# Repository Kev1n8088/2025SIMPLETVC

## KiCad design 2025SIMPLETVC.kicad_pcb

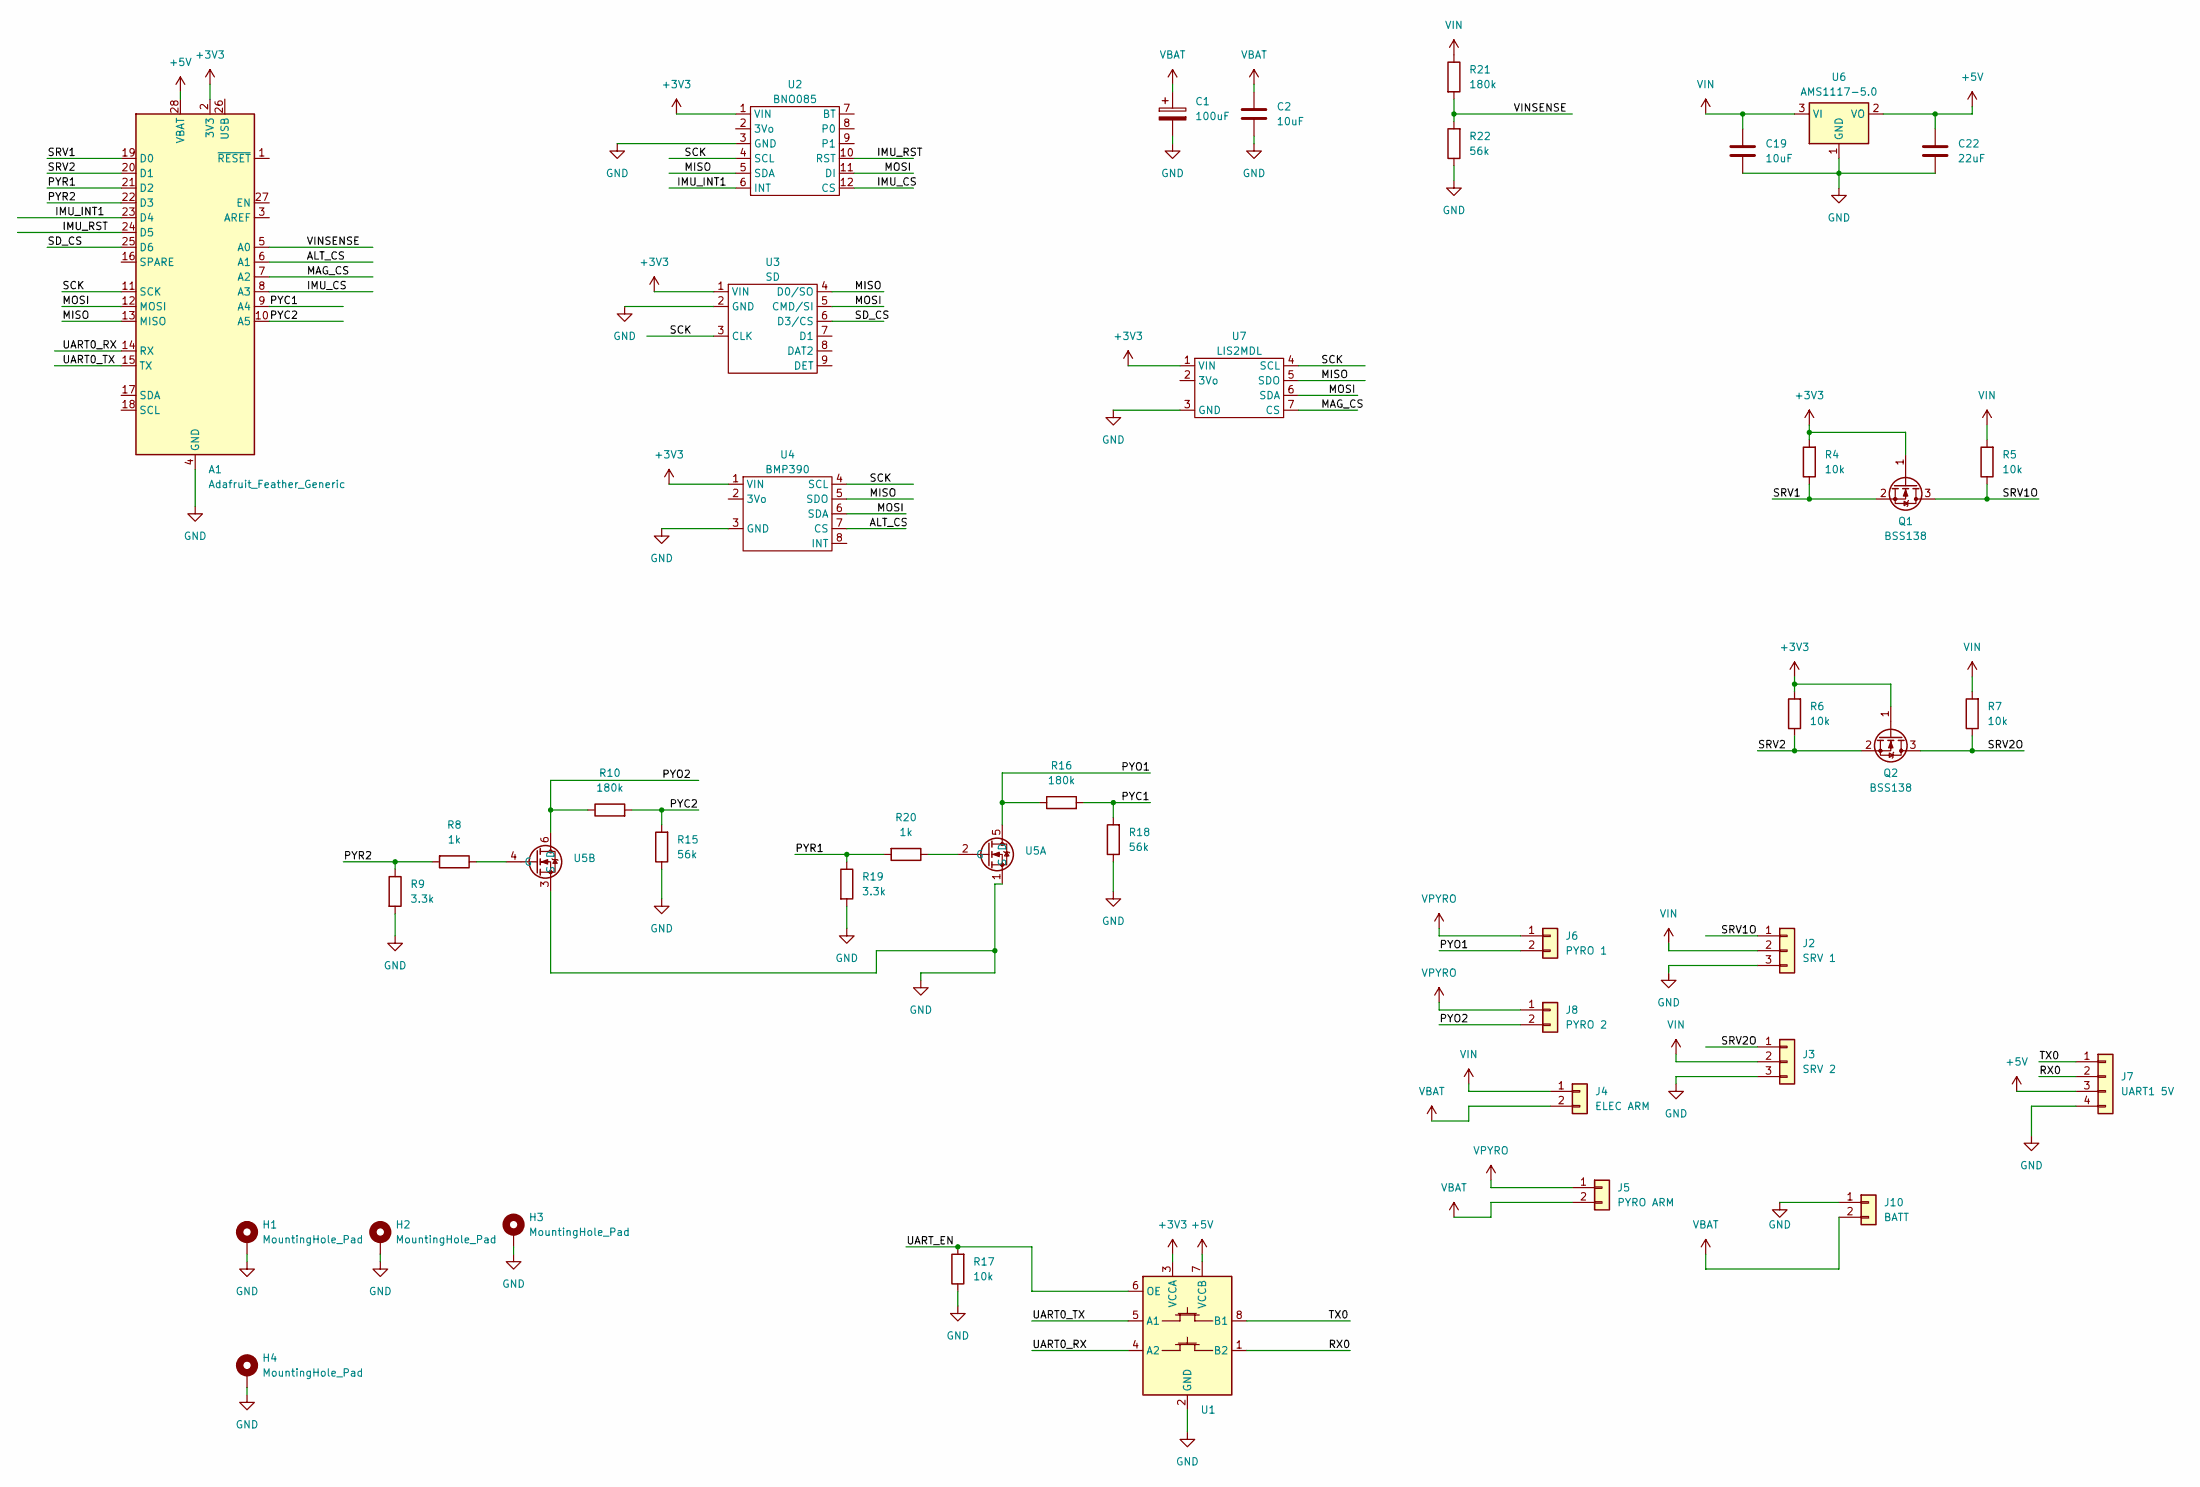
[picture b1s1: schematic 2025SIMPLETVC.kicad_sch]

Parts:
A1: Adafruit_Feather_Generic; Adafruit_Feather
C1: 100uF; CP_Radial_D8.0mm_P5.00mm
C2, C19: 10uF; C_0402_1005Metric
C22: 22uF; C_0402_1005Metric
H1, H2, H3, H4: MountingHole_Pad; MountingHole_4.3mm_M4_DIN965_Pad_TopBottom
J2: SRV 1; JST_XH_B3B-XH-AM_1x03_P2.50mm_Vertical
J3: SRV 2; JST_XH_B3B-XH-AM_1x03_P2.50mm_Vertical
J4: ELEC ARM; JST_XH_B2B-XH-AM_1x02_P2.50mm_Vertical
J5: PYRO ARM; JST_XH_B2B-XH-AM_1x02_P2.50mm_Vertical
J6: PYRO 1; JST_XH_B2B-XH-AM_1x02_P2.50mm_Vertical
J7: UART1 5V; JST_PH_B4B-PH-K_1x04_P2.00mm_Vertical
J8: PYRO 2; JST_XH_B2B-XH-AM_1x02_P2.50mm_Vertical
J10: BATT; AMASS_XT30U-F_1x02_P5.0mm_Vertical
Q1, Q2: BSS138; SOT-23
R4, R5, R6, R7, R17: 10k; R_0402_1005Metric
R8, R20: 1k; R_0402_1005Metric
R9, R19: 3.3k; R_0402_1005Metric
R10, R16, R21: 180k; R_0402_1005Metric
R15, R18, R22: 56k; R_0402_1005Metric
U1: TXS0102DCT; SSOP-8_2.95x2.8mm_P0.65mm
U2: BNO085; BNO085_Breakout_Footprint
U3: SD; SD_Breakout_Footprint
U4: BMP390; BMP390_Breakout_Footprint
U5: SQJ500AEP-T1_GE3_VIS
U6: AMS1117-5.0; SOT-223-3_TabPin2
U7: LIS2MDL; LIS2MDL_Breakout_Footprint

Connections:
+3V3: A1.2 (3V3), Q1.1 (G), Q2.1 (G), R4.2, R6.2, U1.3 (VCCA), U2.1 (VIN), U3.1 (VIN), U4.1 (VIN), U7.1 (VIN)
+5V: A1.28 (VBAT), C22.1, J7.3, U1.7 (VCCB), U6.2 (VO)
/ALT_CS: A1.6 (A1), U4.7 (CS)
/IMU_CS: A1.8 (A3), U2.12 (CS)
/IMU_INT1: A1.23 (D4), U2.6 (INT)
/IMU_RST: A1.24 (D5), U2.10 (RST)
/MAG_CS: A1.7 (A2), U7.7 (CS)
/MISO: A1.13 (MISO), U2.5 (SDA), U3.4 (D0/SO), U4.5 (SDO), U7.5 (SDO)
/MOSI: A1.12 (MOSI), U2.11 (DI), U3.5 (CMD/SI), U4.6 (SDA), U7.6 (SDA)
/PYC1: A1.9 (A4), R16.2, R18.2
/PYC2: A1.10 (A5), R10.2, R15.2
/PYO1: J6.2, R16.1, U5.5 (D)
/PYO2: J8.2, R10.1, U5.6 (D)
/PYR1: A1.21 (D2), R19.1, R20.2
/PYR2: A1.22 (D3), R8.2, R9.1
/RX0: J7.2, U1.1 (B2)
/SCK: A1.11 (SCK), U2.4 (SCL), U3.3 (CLK), U4.4 (SCL), U7.4 (SCL)
/SD_CS: A1.25 (D6), U3.6 (D3/CS)
/SRV1: A1.19 (D0), Q1.2 (S), R4.1
/SRV1O: J2.1, Q1.3 (D), R5.1
/SRV2: A1.20 (D1), Q2.2 (S), R6.1
/SRV2O: J3.1, Q2.3 (D), R7.1
/TX0: J7.1, U1.8 (B1)
/UART0_RX: A1.14 (RX), U1.4 (A2)
/UART0_TX: A1.15 (TX), U1.5 (A1)
/UART_EN: R17.2, U1.6 (OE)
/VINSENSE: A1.5 (A0), R21.2, R22.2
GND: A1.4 (GND), C1.2, C2.2, C19.2, C22.2, H1.1, H2.1, H3.1, H4.1, J2.3, J3.3, J7.4, J10.1, R9.2, R15.1, R17.1, R18.1, R19.2, R22.1, U1.2 (GND), U2.3 (GND), U3.2 (GND), U4.3 (GND), U5.1 (S), U5.3 (S), U6.1 (GND), U7.3 (GND)
unnamed: R20.1, U5.2 (G)
unnamed: R8.1, U5.4 (G)
VBAT: C1.1, C2.1, J4.2, J5.2, J10.2
VIN: C19.1, J2.2, J3.2, J4.1, R5.2, R7.2, R21.1, U6.3 (VI)
VPYRO: J5.1, J6.1, J8.1

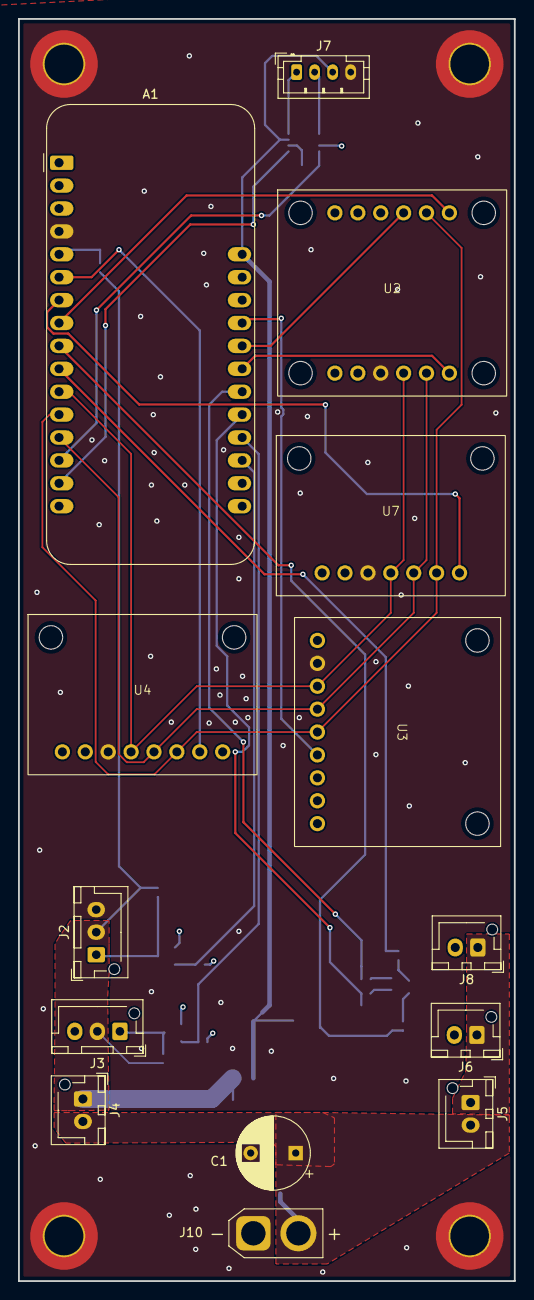
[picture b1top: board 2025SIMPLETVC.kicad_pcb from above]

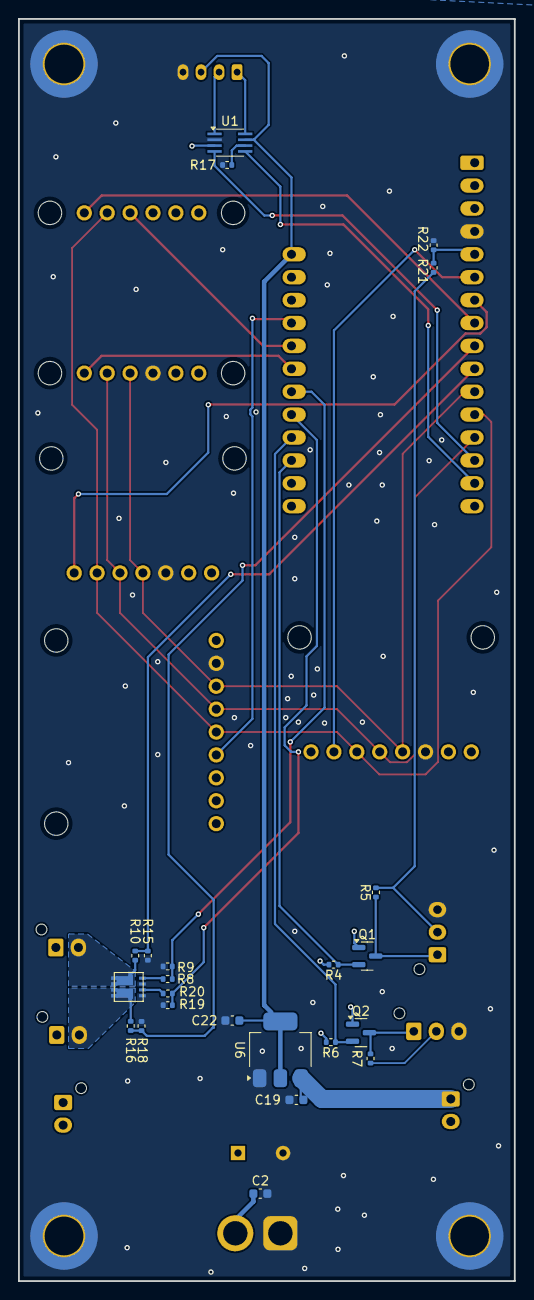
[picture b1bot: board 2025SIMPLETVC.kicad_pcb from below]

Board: 4 copper layers, 55.0 x 140.0 mm, 41 parts (23 on the bottom side), 33 nets.

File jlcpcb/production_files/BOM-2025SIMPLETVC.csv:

Comment,Designator,Footprint,LCSC,Quantity
56k,"R15,R18,R22",R_0402_1005Metric,C114756,3
1k,"R20,R8",R_0402_1005Metric,C11702,2
180k,"R10,R16,R21",R_0402_1005Metric,C138046,3
BSS138,"Q1,Q2",SOT-23,C193381,2
10k,"R17,R4,R5,R6,R7",R_0402_1005Metric,C25744,5
3.3k,"R19,R9",R_0402_1005Metric,C25890,2
TXS0102DCT,U1,SSOP-8_2.95x2.8mm_P0.65mm,C324082,1
~,U5,SQJ500AEP-T1_GE3_VIS,C3289529,1
AMS1117-5.0,U6,SOT-223-3_TabPin2,C6187,1
22uF,C22,C_0603_1608Metric,C84419,1
10uF,"C19,C2",C_0603_1608Metric,C96446,2

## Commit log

2025-04-14 basic design completed
2025-04-22 v1.0 finished
